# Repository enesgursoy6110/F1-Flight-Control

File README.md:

It can be used on all flight platforms. Control and telemetry design with Low Power communication module.

RFM69HCW ISM TRANSCEIVER MODULE  :
https://cdn.sparkfun.com/datasheets/Wireless/General/RFM69HCW-V1.1.pdf

FGPMMOPA6H GPS MODULE: 
https://cdn-shop.adafruit.com/datasheets/GlobalTop-FGPMMOPA6H-Datasheet-V0A.pdf

MPL3115A2 Altitude/Pressure Sensor: 
https://cdn.sparkfun.com/datasheets/Sensors/Pressure/MPL3115A2.pdf

MPU6050 Axis Acceleration and Gyro: 
https://invensense.tdk.com/wp-content/uploads/2015/02/MPU-6000-Datasheet1.pdf

HMC6343 3-AXIS DIGITAL COMPASS SOLUTION : 
https://cdn.sparkfun.com/datasheets/Sensors/Magneto/HMC6343.pdf

STM32F103C8T6: 
https://www.st.com/resource/en/datasheet/stm32f103c8.pdf
 
Resources that I have used : https://www.adafruit.com/ , https://www.sparkfun.com/ , https://www.snapeda.com/home/ , https://componentsearchengine.com/

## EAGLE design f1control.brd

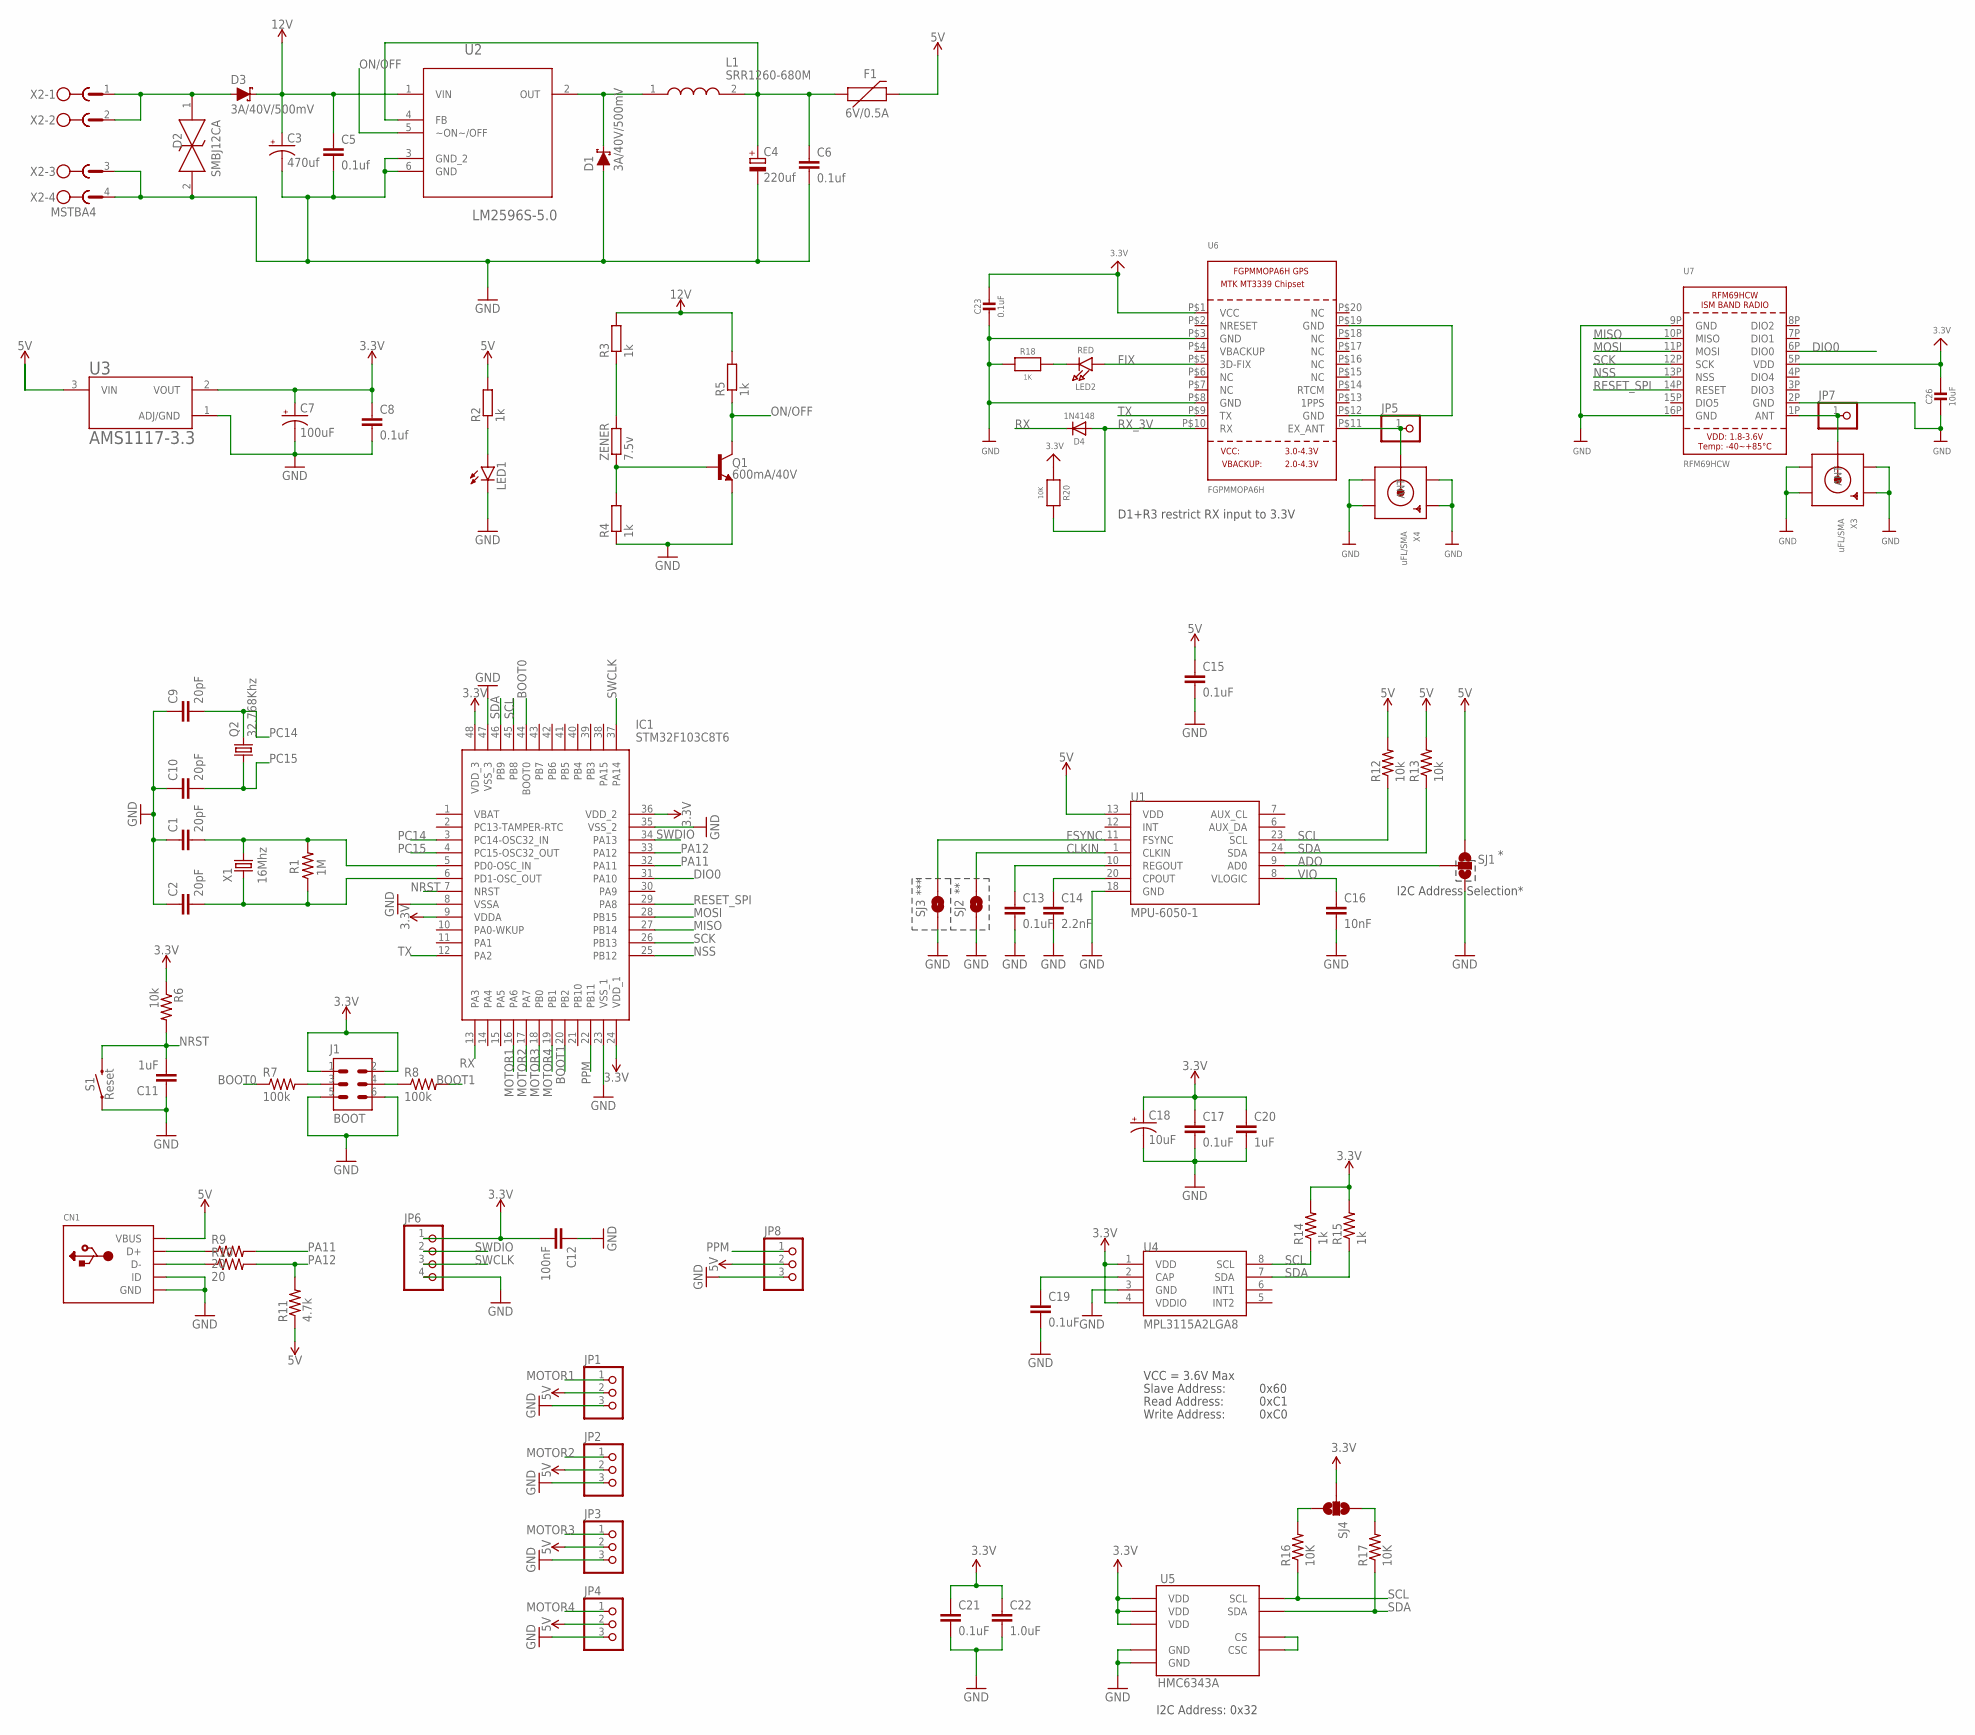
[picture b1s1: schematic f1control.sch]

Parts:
C1, C2, C9, C10: 20pF; C0603
C3: 470uf; E5-8,5
C4: 220uf; 153CLV-1014
C5, C6, C8: 0.1uf; C0805
C7: 100uF; NIC_10X10.5_CAP
C11: 1uF; C0603
C12: 100nF; C0603
C13, C15, C21: 0.1uF; 0603-CAP
C14: 2.2nF; 0603-CAP
C16: 10nF; 0603-CAP
C17, C19: 0.1uF; 0402-CAP
C18: 10uF; EIA3216
C20: 1uF; 0402-CAP
C22: 1.0uF; 0603-CAP
C23: 0.1uF; 0805-NO
C26: 10uF; 0805-NO
CN1: USBMINIB; USB-MINIB
D1, D3: 3A/40V/500mV; SMA-DIODE
D2: SMBJ12CA; DIONM5443X244N
D4: 1N4148; SOD-323
F1: 6V/0.5A; 1206
IC1: STM32F103C8T6; QFP50P900X900X160-48N
J1: BOOT; 621006245821
JP1, JP2, JP3, JP4, JP8: PINHD-1X3; 1X03
JP5, JP7: HEADER-1X1ROUND; 1X01_ROUND
JP6: PINHD-1X4; 1X04
L1: SRR1260-680M; INDPM125125X650N
LED1: LEDCHIP-LED0805; CHIP-LED0805
LED2: RED; CHIPLED_0805
Q1: 600mA/40V; SOT23-3
Q2: 32.768Khz; MC-306
R1: 1M; R0603
R2, R3, R4, R5: 1k; R0805
R6: 10k; R0603
R7, R8: 100k; R0603
R9, R10: 20; R0603
R11: 4.7k; R0603
R12, R13: 10k; 0603-RES
R14, R15: 1k; 0402-RES
R16, R17: 10K; 0603-RES
R18: 1K; 0805-NO
R20: 10K; 0805-NO
S1: Reset; TACTILE_SWITCH_SMD_4.5MM
SJ1: SOLDERJUMPER_2WAYPASTE2&3; SJ_3_PASTE2&3
SJ2, SJ3: SOLDERJUMPERTRACE; SJ_2S-TRACE
SJ4: SOLDERJUMPER_2WAYPASTE1&2&3; SJ_3_PASTE1&2&3
U1: MPU-6050-1; QFN-24-4MM2
U2: LM2596S-5.0; TO170P1435X465-6N
U3: AMS1117-3.3; SOT229P700X180-4N
U4: MPL3115A2LGA8; LGA8
U5: HMC6343A; LCC36
U6: FGPMMOPA6H
U7: RFM69HCW; RFMHCW_SMT
X1: 16Mhz; XTAL_HC49
X2: MSTBA4
X3, X4: uFL/SMA; SMA_EDGELAUNCH_UFL
ZENER: 7.5v; 0204/7

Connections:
3.3V: C7.+, C8.1, C12.2, C17.1, C18.A (+), C20.1, C21.1, C22.1, C23.1, C26.1, IC1.9 (VDDA), IC1.24 (VDD_1), IC1.36 (VDD_2), IC1.48 (VDD_3), J1.1, J1.2, JP6.1, R6.1, R14.2, R15.2, R20.1, SJ4.2, U3.2 (VOUT), U4.1 (VDD), U4.4 (VDDIO), U5.3 (VDD), U5.11 (VDD), U5.21 (VDD), U6.P$1 (VCC), U7.5P (VDD)
5V: C15.1, CN1.VBUS, F1.2, JP1.2, JP2.2, JP3.2, JP4.2, JP8.2, R2.2, R11.1, R12.2, R13.2, SJ1.1, U1.13 (VDD), U3.3 (VIN)
12V: C3.+, C5.1, D3.C, R3.2, R5.2, U2.1 (VIN)
ADO: SJ1.2, U1.9 (AD0)
BOOT0: IC1.44 (BOOT0), R7.1
BOOT1: IC1.20 (PB2), R8.2
CLKIN: SJ2.2, U1.1 (CLKIN)
DIO0: IC1.31 (PA10), U7.6P (DIO0)
FIX: LED2.A, U6.P$5 (3D-FIX)
FSYNC: SJ3.2, U1.11 (FSYNC)
GND: C1.1, C2.1, C3.-, C4.-, C5.2, C6.2, C7.-, C8.2, C9.1, C10.1, C11.1, C12.1, C13.2, C14.2, C15.2, C16.2, C17.2, C18.C (-), C19.2, C20.2, C21.2, C22.2, C23.2, C26.2, CN1.GND, CN1.ID, D1.A, D2.2, IC1.8 (VSSA), IC1.23 (VSS_1), IC1.35 (VSS_2), IC1.47 (VSS_3), J1.5, J1.6, JP1.3, JP2.3, JP3.3, JP4.3, JP6.4, JP8.3, LED1.C, Q1.2 (E), R4.1, R18.1, S1.2 (1), S1.3 (1), SJ1.3, SJ2.1, SJ3.1, U1.18 (GND), U2.3 (GND_2), U2.6 (GND), U3.1 (ADJ/GND), U4.3 (GND), U5.25 (GND), U5.29 (GND), U6.P$3 (GND), U6.P$8 (GND), U7.2P (GND), U7.9P (GND), U7.16P (GND), X2.3, X2.4, X3.GND@1 (GND1), X3.GND@2 (GND2), X3.GND@3 (GND3), X3.GND@4 (GND4), X4.GND@1 (GND1), X4.GND@2 (GND2), X4.GND@3 (GND3), X4.GND@4 (GND4)
MISO: IC1.27 (PB14), U7.10P (MISO)
MOSI: IC1.28 (PB15), U7.11P (MOSI)
MOTOR1: IC1.16 (PA6), JP1.1
MOTOR2: IC1.17 (PA7), JP2.1
MOTOR3: IC1.18 (PB0), JP3.1
MOTOR4: IC1.19 (PB1), JP4.1
unnamed: J1.3, R7.2
unnamed: C1.2, IC1.5 (PD0-OSC_IN), R1.2, X1.2
unnamed: C2.2, IC1.6 (PD1-OSC_OUT), R1.1, X1.1
unnamed: D1.C, L1.1, U2.2 (OUT)
unnamed: LED1.A, R2.1
unnamed: Q1.1 (B), R4.2, ZENER.1
unnamed: C4.+, C6.1, F1.1, L1.2, U2.4 (FB)
unnamed: R3.1, ZENER.2
unnamed: D2.1, D3.A, X2.1, X2.2
unnamed: J1.4, R8.1
unnamed: C14.1, U1.20 (CPOUT)
unnamed: CN1.D+, R9.1
unnamed: CN1.D-, R10.1
unnamed: C13.1, U1.10 (REGOUT)
unnamed: C19.1, U4.2 (CAP)
unnamed: U5.22 (CS), U5.35 (CSC)
unnamed: R16.2, SJ4.3
unnamed: R17.2, SJ4.1
unnamed: LED2.C, R18.2
unnamed: JP5.1, U6.P$11 (EX_ANT), X4.P (ANT)
unnamed: JP7.1, U7.1P (ANT), X3.P (ANT)
unnamed: U6.P$12 (GND), U6.P$19 (GND)
NRST: C11.2, IC1.7 (NRST), R6.2, S1.1 (2), S1.4 (2)
NSS: IC1.25 (PB12), U7.13P (NSS)
ON/OFF: Q1.3 (C), R5.1, U2.5 (~ON~/OFF)
PA11: IC1.32 (PA11), R9.2
PA12: IC1.33 (PA12), R10.2, R11.2
PC14: C9.2, IC1.3 (PC14-OSC32_IN), Q2.4 (2)
PC15: C10.2, IC1.4 (PC15-OSC32_OUT), Q2.1
PPM: IC1.22 (PB11), JP8.1
RESET_SPI: IC1.29 (PA8), U7.14P (RESET)
RX: D4.C, IC1.13 (PA3)
RX_3V: D4.A, R20.2, U6.P$10 (RX)
SCK: IC1.26 (PB13), U7.12P (SCK)
SCL: IC1.45 (PB8), R12.1, R14.1, R16.1, U1.23 (SCL), U4.8 (SCL), U5.32 (SCL)
SDA: IC1.46 (PB9), R13.1, R15.1, R17.1, U1.24 (SDA), U4.7 (SDA), U5.36 (SDA)
SWCLK: IC1.37 (PA14), JP6.3
SWDIO: IC1.34 (PA13), JP6.2
TX: IC1.12 (PA2), U6.P$9 (TX)
VIO: C16.1, U1.8 (VLOGIC)

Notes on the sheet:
I2C Address Selection*
***
VCC = 3.6V Max
Read Address:
Write Address:
Slave Address:
0x60
0xC1
0xC0
I2C Address: 0x32
D1+R3 restrict RX input to 3.3V

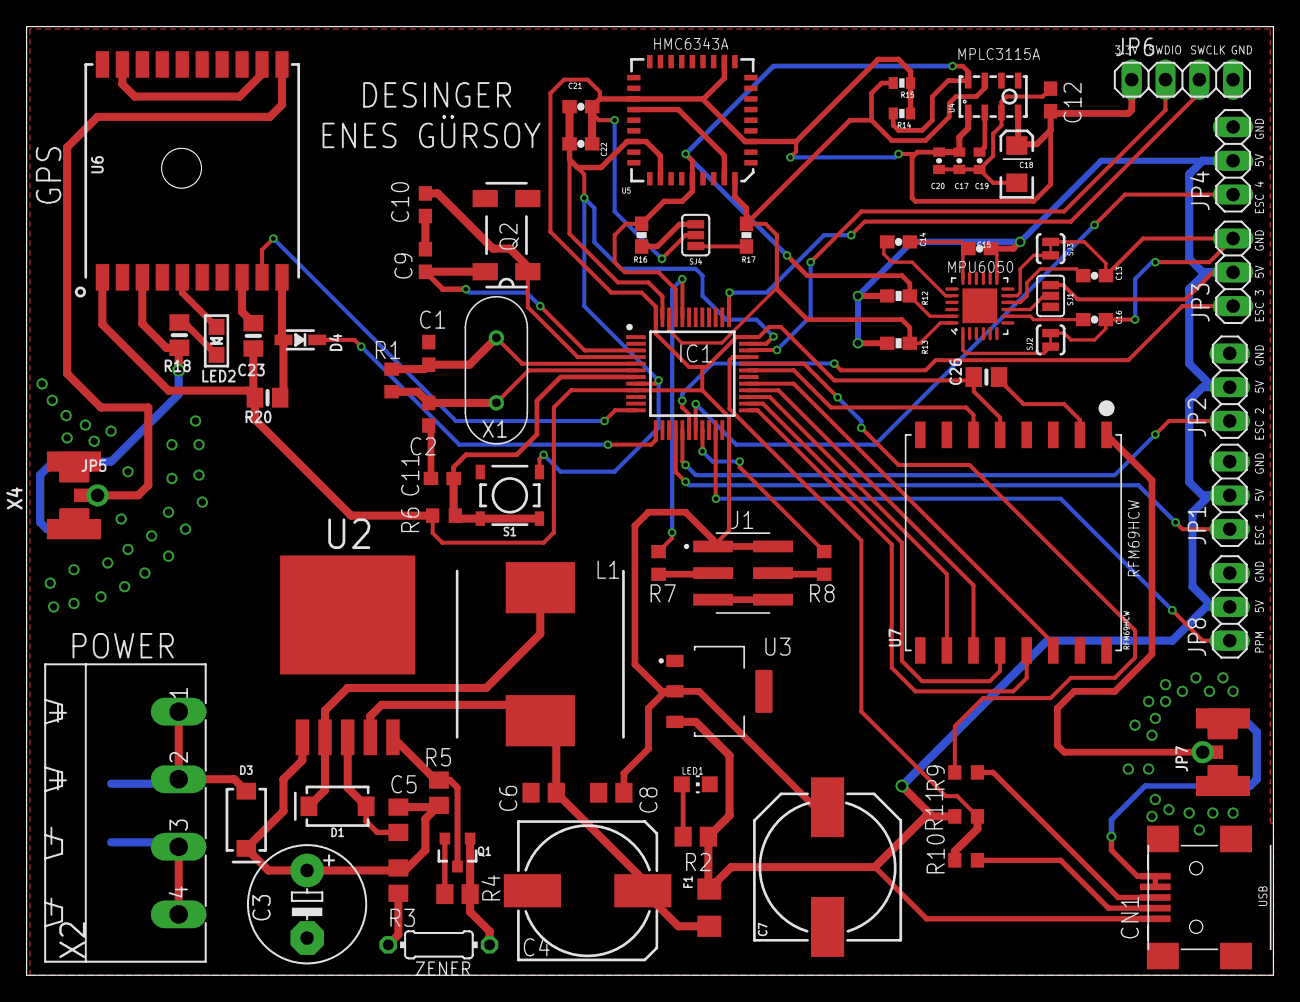
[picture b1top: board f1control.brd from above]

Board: 2 copper layers, 93.7 x 71.3 mm, 81 parts (1 on the bottom side), 57 nets.

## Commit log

2020-04-03 ReadMe
    It can be used on all flight platforms. Control and telemetry design with Low Power communication module.
    RFM69HCW ISM TRANSCEIVER MODULE :
    https://cdn.sparkfun.com/datasheets/Wireless/General/RFM69HCW-V1.1.pdf
    FGPMMOPA6H GPS MODULE:
    https://cdn-shop.adafruit.com/datasheets/GlobalTop-FGPMMOPA6H-Datasheet-V0A.pdf
    MPL3115A2 Altitude/Pressure Sensor:

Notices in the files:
parts and their libraries:
SparkFun-DiscreteSemi: Licensing: Creative Commons ShareAlike 4.0 International - https://creativecommons.org/licenses/by-sa/4.0
SparkFun-Sensors: Licensing: CC v3.0 Share-Alike You are welcome to use this library for commercial purposes.
